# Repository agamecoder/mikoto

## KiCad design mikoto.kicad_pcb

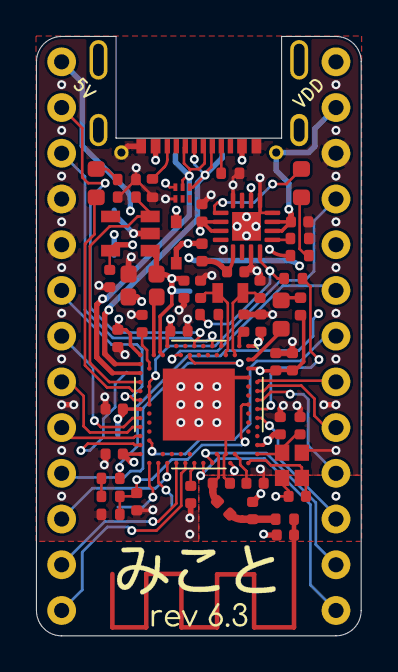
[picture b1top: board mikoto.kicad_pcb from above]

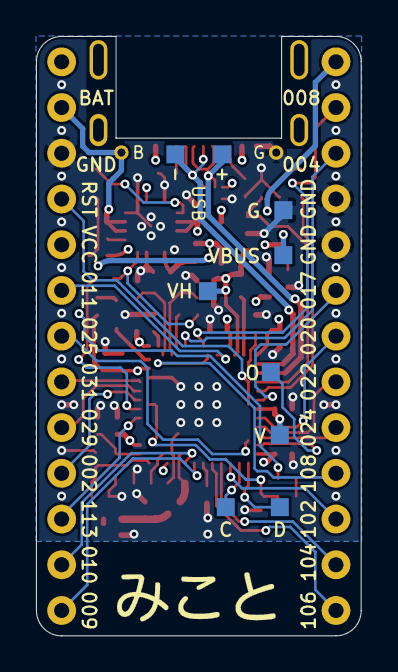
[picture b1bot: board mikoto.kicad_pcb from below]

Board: 4 copper layers, 18.0 x 33.3 mm, 70 parts (10 on the bottom side), 61 nets.

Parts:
AE1: Antenna; 2.4GHz-meander-antenna-v2
C1, C13, C14, C20, C24, C25, C26: 4.7uF; Capacitor_0402_1005M-nosilk
C2, C3, C4, C10: 100nF; Capacitor_0402_1005M-nosilk
C5, C9: 1pF; Capacitor_0402_1005M-nosilk
C6, C7, C17, C18: 15pF; Capacitor_0402_1005M-nosilk
C8, C15, C23: 1uF; Capacitor_0402_1005M-nosilk
C11: 100pF; Capacitor_0402_1005M-nosilk
C12: 1nF; Capacitor_0402_1005M-nosilk
C16: 47nF; Capacitor_0402_1005M-nosilk
C19: 10nF; Capacitor_0402_1005M-nosilk
C21: 10uF; Capacitor_0603_1608M-nosilk
C22: 1.5pF; Capacitor_0402_1005M-nosilk
D1: BLUE; LED_0603_1608Metric-nosilk
D3: ORANGE; LED_0603_1608Metric-nosilk
D5: PMEG4010CEJ; D_SOD-323F-nosilk
DUMMY1: logo_front; mikoto-logo
DUMMY2: logo_back; mikoto-logo
DUMMY3: revision_number; revision-number
F1: 500mA hold; Fuse_0402_1005Metric
J1: USB_C_Receptacle_USB2.0; USB-C_C168688
J4, J5: PTH; PTH-0.8_0.45mm
L1: 3.9nH; Inductor_0402_1005M-nosilk
L2: 15nH; Inductor_0402_1005M-nosilk
L3, L4: 10uH; Inductor_0603_1608M-nosilk
NT1: NetTie_2; net-tie-2-tiny
R1: 3.9k; Resistor_0402_1005M-nosilk
R2, R3, R12: 2M; Resistor_0402_1005M-nosilk
R4: 10M; Resistor_0402_1005M-nosilk
R5: 1.5k; Resistor_0402_1005M-nosilk
R6, R7, R8: 10k; Resistor_0402_1005M-nosilk
R9, R10: 5.1k; Resistor_0402_1005M-nosilk
R11: 0R; Resistor_0402_1005M-nosilk
TP1, TP2, TP3, TP4, TP5, TP6, TP7, TP8, TP9: PAD; TestPoint_Pad_1.0x1.0mm-nosilk
U1: nRF52840; AQFN-73-1EP_7x7mm_P0.5mm_NRF52840-custom
U2: BQ24075RGT; VQFN-16-1EP_3x3mm_P0.5mm_EP1.6x1.6mm
U3: XC6220B331MR; SOT-23-5
U4: mikoto-pins
U5: ESDR0502NMUTAG; UDFN-6_1.2x1.0mm_P0.4mm
Y1: 32MHz; Crystal_SMD_2016-4Pin_2.0x1.6mm
Y2: 32.768 kHz; Crystal_SMD_2012-2Pin_2.0x1.2mm

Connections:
/ANT: AE1.1 (A), C22.2, R11.2
/CC1: J1.A5 (CC1), R9.1
/CC2: J1.B5 (CC2), R10.1
BAT_VOLT: C19.2, R3.2, R4.1, U1.B13 (AIN1/P0.03)
BLUE_LED: D1.2 (A), U1.AD10 (P0.15)
CHARGE_CTRL_1: R7.1, U1.G1 (P0.26)
CHARGE_CTRL_2: R1.2, U1.A14 (P1.15)
EXT_5V: D5.1 (K), F1.2, U4.1 (EXT_5V)
GND: C1.1, C2.1, C3.1, C4.2, C5.1, C6.2, C7.2, C8.2, C10.2, C11.2, C12.2, C13.2, C14.1, C15.1, C16.1, C17.1, C18.1, C19.1, C20.1, C21.1, C22.1, C23.2, C24.1, C25.1, C26.1, J1.A1 (GND), J5.1, NT1.2, R2.2, R4.2, R5.1, R8.2, R9.2, R10.2, TP5.1, U1.B7 (VSS), U1.EP (VSS), U2.4 (~CE), U2.5 (EN2), U2.8 (VSS), U2.15 (SYSOFF), U2.17 (VSS), U3.2 (GND), U4.4 (GND), U4.5 (GND), U4.24 (GND), U5.1 (GND), Y1.2, Y1.4
unnamed: C5.2, L1.1, R11.1
unnamed: C6.1, U1.B24 (XC1), Y1.1
unnamed: C7.1, U1.A23 (XC2), Y1.3
unnamed: C9.2, L1.2, U1.H23 (ANT)
unnamed: C10.1, U1.C1 (DEC1)
unnamed: C11.1, U1.D23 (DEC3)
unnamed: C12.1, U1.N24 (DEC5)
unnamed: C13.1, U1.AC5 (DECUSB)
unnamed: C15.2, C16.2, L2.1, U1.B5 (DEC4), U1.E24 (DEC6)
unnamed: C17.2, U1.D2 (XL1/P0.00), Y2.1
unnamed: C18.2, U1.F2 (XL2/P0.01), Y2.2
unnamed: C23.1, F1.1, U2.13 (IN)
unnamed: D1.1 (K), R5.2
unnamed: D3.1 (K), U2.9 (~CHG)
unnamed: D3.2 (A), R6.2
unnamed: L2.2, L3.1
unnamed: L3.2, U1.B3 (DCC)
unnamed: L4.2, U1.AB2 (DCCH)
unnamed: R1.1, R7.2, U2.16 (ISET)
unnamed: R8.1, U2.1 (TS)
unnamed: R3.1, R12.2
P0.02: U1.A12 (AIN0/P0.02), U4.17
P0.04: U1.J1 (AIN2/P0.04), U4.3
P0.08: U1.N1 (P0.08), U4.2
P0.09: U1.L24 (NFC1/P0.09), U4.14
P0.10: U1.J24 (NFC2/P0.10), U4.15
P0.11: U1.T2 (TRACEDATA2/P0.11), U4.21
P0.17: U1.AD12 (P0.17), U4.6
P0.20: U1.AD16 (P0.20), U4.7
P0.22: U1.AD18 (P0.22), U4.8
P0.24: U1.AD20 (P0.24), U4.9
P0.25: U1.AC21 (P0.25), U4.20
P0.29: U1.A10 (AIN5/P0.29), U4.18
P0.31: U1.A8 (AIN7/P0.31), U4.19
P1.02: U1.W24 (P1.02), U4.11
P1.04: U1.U24 (P1.04), U4.12
P1.06: U1.R24 (P1.06), U4.13
P1.08: U1.P2 (P1.08), U4.10
P1.13: U1.A16 (P1.13), U4.16
PPH_VCC: C20.2, U3.5 (VOUT), U4.22 (VCC)
PPH_VCC_CTRL: R2.1, U1.AD8 (P0.13), U3.3 (CE)
RESET: U1.AC9 (P0.14), U1.AC11 (P0.16), U1.AC13 (P0.18/~RESET), U4.23 (RST)
SWC: TP1.1, U1.AA24 (SWDCLK)
SWD: TP2.1, U1.AC24 (SWDIO)
SWO: TP9.1, U1.AD22 (TRACEDATA0/P1.00)
USB_D+: J1.A6 (D+), J1.B6 (D+), TP6.1, U1.AD6 (D+), U5.5 (D+)
USB_D-: J1.A7 (D-), J1.B7 (D-), TP4.1, U1.AD4 (D-), U5.4 (D-)
VBAT: C26.2, J4.1, R12.1, U2.2 (BAT), U2.3 (BAT), U4.25 (RAW)
VBUS: C14.2, D5.2 (A), J1.A4 (VBUS), TP8.1, U1.AD2 (VBUS), U5.6 (VBUS)
VDDH: C21.2, C24.2, C25.2, R6.1, TP7.1, U1.Y2 (VDDH), U2.6 (EN1), U2.10 (OUT), U2.11 (OUT), U3.1 (VIN)
VDD_NRF: C1.2, C2.2, C3.2, C4.1, C8.1, L4.1, TP3.1, U1.A22 (VDD), U1.AD14 (VDD), U1.AD23 (VDD), U1.B1 (VDD), U1.W1 (VDD), U4.26 (VDD)
VSS_PA: C9.1, NT1.1, U1.F23 (VSS_PA)

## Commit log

2022-01-12 rev 6.3 (for oshpark)
    tweak antenna feed layout for oshpark board stackup.
